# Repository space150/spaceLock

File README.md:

# spaceLock

The goal of this project is to use the new Apple Watch to interact and open doors in the physical space. This project includes the iOS app and WatchKit extension, and a RFduino application and solenoid circuit. Using the combination of these, you can turn any door into a “smart” door, and a seamless physical to digital connection.

This project is a product of spaceLab, space150’s research and development division.

# Directory Structure

* <code>arduino</code> contains the physical lock arduino sketch and library dependencies. The lock itself is running on a RFDuino, other platforms will be supported in the future.

* <code>docs</code> contains an EAGL schematic for a reference implementation of the RFDuino integrated with a selenoid lock. Works with a 12VDC solenoid up to 1 amp.

* <code>ios</code> contains the iOS iPhone application with WatchKit extension.

# Security & Known Issues

This project is more of a "proof of concept" in its current state. A few key items need to be addressed to ensure a secure implementation:

* The AES encryption keys are stored in a plist file within the application bundle. This will in the future be changed so that the keys only reside on a secure server. Once downloaded the application will instead store them in the system Keychain.
* The arduino lock currently has no way of updating its internal clock to match wall-clock time. This prevents us from verifying the timestamp of the encrypted commands. An addition of a Wifi module and NTP client will be added in the future so that the unlock/lock commands are time-sensitive, this will prevent replay attacks.
* There are probably many more security issues, if you do find one or have a suggestion, feel free to send a pull request or email to shawn.roske@space150.com.

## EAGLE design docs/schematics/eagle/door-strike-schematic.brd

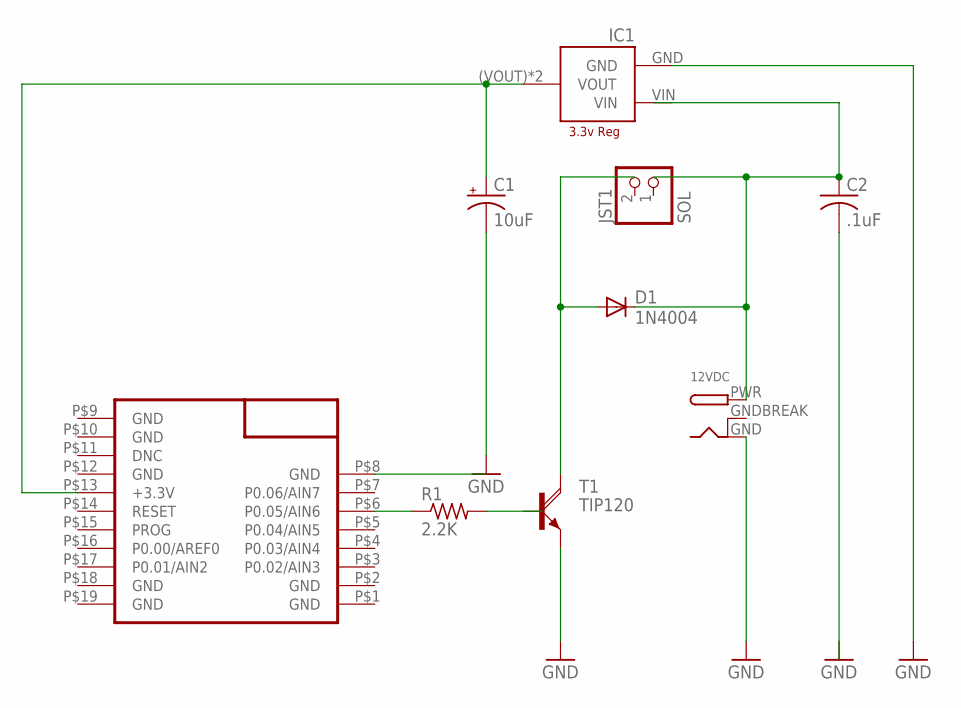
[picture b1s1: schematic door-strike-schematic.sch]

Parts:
12VDC: DCBARRELPTH; DCJACK_2MM_PTH
C1: 10uF; E2-5
C2: .1uF; C102-054X133
D1: 1N4004; DO41-10
IC1: LD1117; LD1117SOT-223
JST1: SOL; JST-PH-2-THM
R1: 2.2K; 0207/7
T1: TIP120; TO220AH
U$2: RFD22301; RFD21733

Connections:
GND: 12VDC.GND, C1.-, IC1.GND, T1.E
GNDBREAK: 12VDC.GNDBREAK
unnamed: R1.1, U$2.P$6 (P0.05/AIN6)
unnamed: D1.A, T1.C
unnamed: C1.+, IC1.(VOUT) (VOUT), IC1.VOUT, U$2.P$13 (+3.3V)
unnamed: 12VDC.PWR, C2.1, D1.C

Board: 2 copper layers, 9 parts (0 on the bottom side), 5 nets, no tracks yet.

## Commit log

2015-03-20 Initial import of RFduino sketch and app with basic AES encryption
2015-03-21 iOS and RFduino now communicate, encryption/decryption works
2015-03-23 added decrypt and encrypt to the security manager, added timestand and command structure to the iphone app
2015-03-23 refactored rfduino sketch so it locks and unlocks the device
2015-03-24 added AES dependency library to git, updated the list view with more information and added the hello handshake to the unlock process
2015-03-24 added google+ integration
2015-03-24 changed signing profile for release
2015-03-31 Added watch kit target
2015-03-31 Added private framework
2015-04-01 Added lock action to the arduino sketch, using pin 6
2015-04-01 initial commit of schematic docs for rfduino solenoid shield
2015-04-02 Added Lock discovery manager, repository and fetched results controller for the iPhone app. added some starter ranging logic
2015-04-02 Updated version 1.0b2
2015-04-03 added HUD to show progress while unlocking, added functionality to the apple watchkit extension, added logic ot clear out locks that are out of range
2015-04-03 bumped build version to 3, cleaned up the lock management code in lock discovery manager
2015-04-03 added error messaging for the watchkit app
2015-04-06 Initial push to integrate design
2015-04-06 Added better cell row layout to iPhone app, added visual states for unlock
2015-04-06 Font/layout fixes
2015-04-06 Temp fix for status bar shenanigans, updating lock header count
2015-04-06 bumped version to 1.0b4
2015-04-06 Knocked in interface for apple watch
2015-04-06 added row states to watch kit app
2015-04-07 Added MMWormhole so the watch kit extension and app now should hand-off control, some layout fixes on the watch kit app
2015-04-07 fixes for iphone 6+ layout
2015-04-07 Changed the discovery manager logic so that it never actually deletes found locks
2015-04-07 added a timeout for missed handshakes
2015-04-07 added better domain auth to google plus services
2015-04-17 added key generation and different keys for each lock
2015-04-21 changed the layout to be more simple, added circular animations on the icon
2015-04-21 added the new startup screen
2015-04-22 cleaned up the lock management and cell view logic so the tableview does not update when unlocking and to clean up the noisy coredata updates
2015-04-22 tweak to the in progress animation
2015-04-22 bumped build to version 8
2015-04-23 Layout changes per Marc
2015-04-23 bumped version to build 9
2015-04-24 updated schema with RFduino component and caps for voltage regulation
2015-04-24 removing eagle backup files
2015-04-24 cleaning up unused assets, added licensing and stub read
2015-04-24 added general description to readme
2015-04-24 Added more detail to the README
2015-04-24 initial import
2015-04-24 Spelling Error
2015-04-27 Neglected to include the Default-Keychain.plist resource in the WatchKit extension
2015-04-28 Added key for spaceLab room, bumped to version 11
2015-05-18 Large refactoring to make the app more usable
    - Removed login and startup screen
    - Added key list and ability to generate keys
    - Changed key list storage from plaintext plist files (I know, I know)
    to the iOS keychain using KeychainAccess
2015-05-18 Accidentally missed the Key list view controller
2015-05-18 deleting a key now also removed the corresponding lock entry
2015-05-19 Added ability to take/assign a photo
2015-05-19 now cleans up the images on delete, disabled save button on save
2015-05-19 added validations to the lock id and name text fields
2015-05-19 Bug fixes for images, image path is now stored in cordite
2015-05-19 adding license to new files
2015-05-19 Added dropbox integration with upload, still need to add download/merge
2015-05-19 cleaned up board organization and added label for LD1117 IC
2015-05-19 more schematic organization
2015-05-19 added merging of dropbox info
2015-05-19 Updated icon and cleaned up the dropbox integration when the app is unlinked
2015-05-19 Changed app ID
2015-05-20 Updated icons for watch kit app
2015-05-29 working on local notifications with unlock actions
2015-05-29 add gitignore
2015-06-03 Replaced KeychainAccess with a simplified keychain implementation in LKSecurityManager, added keychain access capability to app and extension profiles
2015-06-05 Changed keychain access to use generic password profile instead of private key profile, it should now clean up old keys before adding new ones (preventing an error)
2015-06-05 Added "no results" views to the door and lock list
2015-06-05 Added dropbox logo and messaging for sync
2015-06-05 Typo in instructions
2015-06-08 Bumped version to 15, fixed layout issue with Dropbox Link overlay, fixed issue with Dropbox integration
2015-06-09 Bumped to 1.0b16
2015-09-17 Swift version update check
2015-09-17 Swift updates and working build for iOS 9 and Xcode 7
2015-10-08 Swift 2 updates
2015-10-08 proper team selections in Xcode
2015-11-11 Update swift for iOS 9
2015-11-11 bump to 12
2015-12-21 added space150 vip lock key
2015-12-21 updated build for space150-vip door
2017-01-03 Bring iOS and Arduino projects up to modern syntax
2017-03-07 Add timestamp verification
2017-03-07 Add Simblee support
